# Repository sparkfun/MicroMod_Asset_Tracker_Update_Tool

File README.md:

# MicroMod Asset Tracker Firmware Update Tool

[*SparkFun MicroMod Update Tool (DEV-17725)*](https://www.sparkfun.com/products/17725)

A dummy Processor Board which will simplify firmware updates for the SARA-R5 on the [MicroMod Asset Tracker Carrier Board](https://www.sparkfun.com/products/17272).

The board carries a CH340C USB-Serial converter to act as the bridge between the USB-C interface on the carrier board and the 8-wire UART interface on the SARA-R5.

Power for the SARA can be enabled via a push-button on the carrier board.

The firmware can be updated with [EasyFlash](https://www.u-blox.com/sites/default/files/SARA-R5-FW-Update_AppNote_%28UBX-20033314%29.pdf).

The tool will also make it easy for anyone wanting to use [m-center](https://www.u-blox.com/en/product/m-center) to communicate with the SARA.

## Repository Contents

* **/Hardware** - Eagle PCB, SCH and LBR design files
* **LICENSE.md** contains the licence information

## Documentation

* **[Hookup Guide](https://learn.sparkfun.com/tutorials/micromod-update-tool-hookup-guide)** - A basic Hookup Guide for the MicroMod Update Tool.
* **[Getting Started with MicroMod](https://learn.sparkfun.com/tutorials/getting-started-with-micromod)** - A tutorial to help you get started with the MicroMod Ecosystem.
* **[Designing with MicroMod](https://learn.sparkfun.com/tutorials/designing-with-micromod)** - A tutorial to walk you through the specs of the MicroMod processor and carrier board as well as the basics of incorporating the MicroMod form factor into your own PCB designs.

## Product Versions

* **[DEV-17725](https://www.sparkfun.com/products/17725)** - Initial release of the MicroMod Update Tool

## License Information

This product is _**open source**_!

Please review the LICENSE.md file for license information.

If you have any questions or concerns on licensing, please contact technical support on our [SparkFun forums](https://forum.sparkfun.com/viewforum.php?f=152).

Distributed as-is; no warranty is given.

- Your friends at SparkFun.

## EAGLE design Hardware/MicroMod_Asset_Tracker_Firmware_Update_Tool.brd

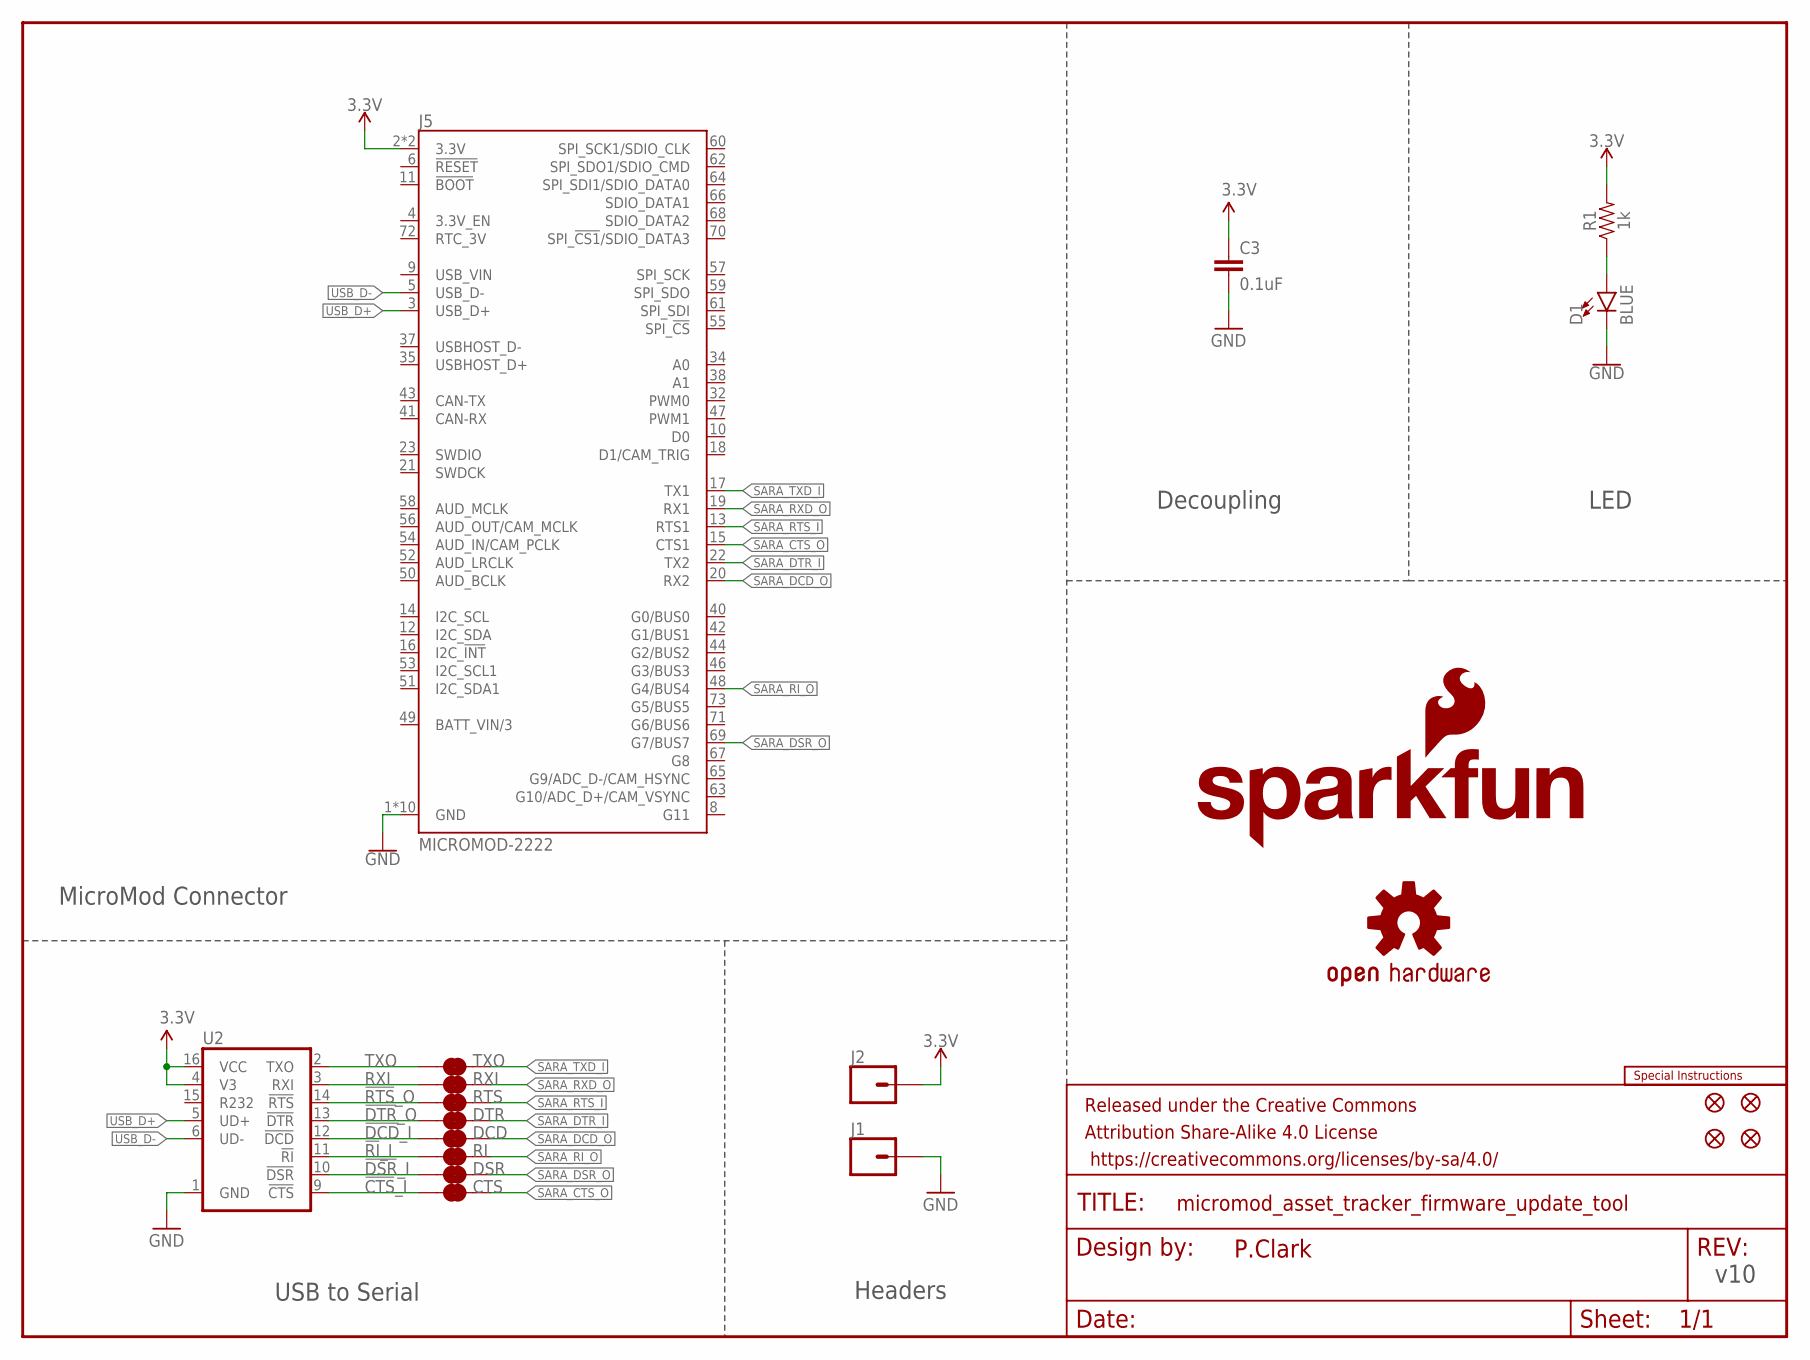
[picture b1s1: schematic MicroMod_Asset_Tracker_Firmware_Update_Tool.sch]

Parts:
C3: 0.1uF; 0603
CTS: JUMPER-COMBO_2_NC_TRACE; COMBO-JUMPER_2_NC_TRACE
D1: BLUE; LED-0603
DCD: JUMPER-COMBO_2_NC_TRACE; COMBO-JUMPER_2_NC_TRACE
DSR: JUMPER-COMBO_2_NC_TRACE; COMBO-JUMPER_2_NC_TRACE
DTR: JUMPER-COMBO_2_NC_TRACE; COMBO-JUMPER_2_NC_TRACE
FRAME1: FRAME-LETTER; CREATIVE_COMMONS
J1, J2: CONN_01PTH_NO_SILK_YES_STOP; 1X01_NO_SILK
J5: MICROMOD-2222; M.2-CARD-E-22
JP3, JP4, JP5, JP6: FIDUCIAL1X2; FIDUCIAL-1X2
LOGO1: OSHW-LOGOMINI; OSHW-LOGO-MINI
LOGO2: SPECIAL_INSTRUCTIONS-ORDERING; ORDERING_INSTRUCTIONS
LOGO3: SFE_LOGO_NAME_FLAME.1_INCH; SFE_LOGO_NAME_FLAME_.1
R1: 1k; 0603
RI: JUMPER-COMBO_2_NC_TRACE; COMBO-JUMPER_2_NC_TRACE
RTS: JUMPER-COMBO_2_NC_TRACE; COMBO-JUMPER_2_NC_TRACE
RXI: JUMPER-COMBO_2_NC_TRACE; COMBO-JUMPER_2_NC_TRACE
TXO: JUMPER-COMBO_2_NC_TRACE; COMBO-JUMPER_2_NC_TRACE
U2: CH340C; SO016

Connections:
3.3V: C3.1, J2.1, J5.2 (3.3V), J5.74 (3.3V), R1.2, U2.4 (V3), U2.16 (VCC)
!CTS!_I: CTS.1, CTS.3 (1), U2.9 (!CTS)
!DCD!_I: DCD.1, DCD.3 (1), U2.12 (!DCD)
!DSR!_I: DSR.1, DSR.3 (1), U2.10 (!DSR)
!DTR!_O: DTR.1, DTR.3 (1), U2.13 (!DTR)
!RI!_I: RI.1, RI.3 (1), U2.11 (!RI)
!RTS!_O: RTS.1, RTS.3 (1), U2.14 (!RTS)
GND: C3.2, D1.C, J1.1, J5.1 (GND), J5.7 (GND), J5.33 (GND), J5.36 (GND), J5.39 (GND), J5.45 (GND), J5.75 (GND), J5.GND1 (GND), J5.GND2 (GND), J5.GND3 (GND), U2.1 (GND)
unnamed: D1.A, R1.1
RXI: RXI.1, RXI.3 (1), U2.3 (RXI)
SARA_CTS_O: CTS.2, CTS.4 (2), J5.15 (CTS1)
SARA_DCD_O: DCD.2, DCD.4 (2), J5.20 (RX2)
SARA_DSR_O: DSR.2, DSR.4 (2), J5.69 (G7/BUS7)
SARA_DTR_I: DTR.2, DTR.4 (2), J5.22 (TX2)
SARA_RI_O: J5.48 (G4/BUS4), RI.2, RI.4 (2)
SARA_RTS_I: J5.13 (RTS1), RTS.2, RTS.4 (2)
SARA_RXD_O: J5.19 (RX1), RXI.2, RXI.4 (2)
SARA_TXD_I: J5.17 (TX1), TXO.2, TXO.4 (2)
TXO: TXO.1, TXO.3 (1), U2.2 (TXO)
USB_D+: J5.3 (USB_D+), U2.5 (UD+)
USB_D-: J5.5 (USB_D-), U2.6 (UD-)

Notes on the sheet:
v10
USB to Serial
P.Clark
Headers
LED
Decoupling
MicroMod Connector

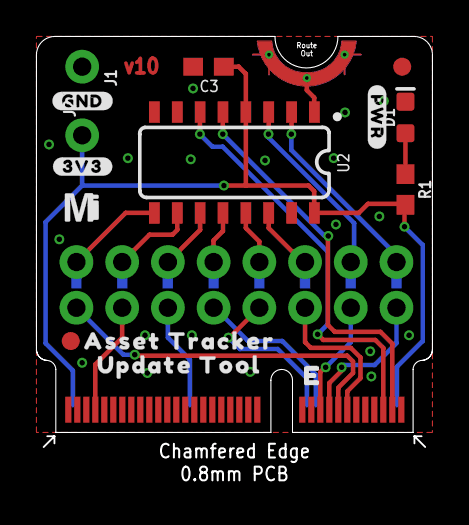
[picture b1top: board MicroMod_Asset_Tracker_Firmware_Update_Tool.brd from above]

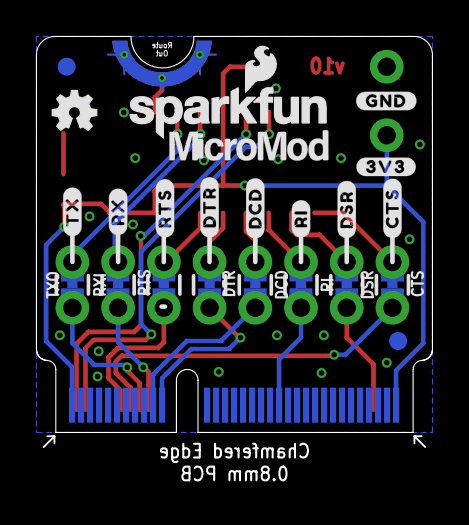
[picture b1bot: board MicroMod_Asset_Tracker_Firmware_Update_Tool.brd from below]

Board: 4 copper layers, 22.0 x 22.8 mm, 40 parts (23 on the bottom side), 21 nets.

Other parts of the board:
U$1: #TX#0
U$2: #RX#0
U$3, U$7: #GND#2
U$4: #DTR#0
U$5: #RI#0
U$6, U$17: #3V3#3
U$8: #PWR#0
U$9: MICROMOD_MI_LOGO_.35
U$10: ASSET_TRACKER0
U$11: UPDATE_TOOL0
U$12: MICROMOD_LOGO_.35
U$14: #CTS#0
U$18: #DSR#0
U$20: #RTS#0
U$23: #DCD#0

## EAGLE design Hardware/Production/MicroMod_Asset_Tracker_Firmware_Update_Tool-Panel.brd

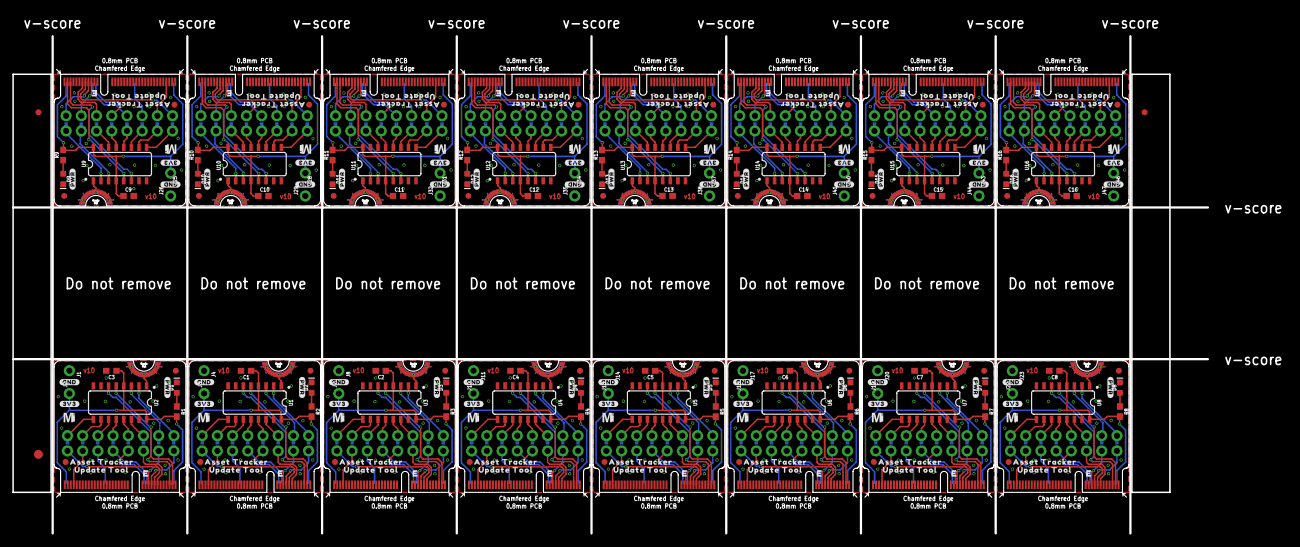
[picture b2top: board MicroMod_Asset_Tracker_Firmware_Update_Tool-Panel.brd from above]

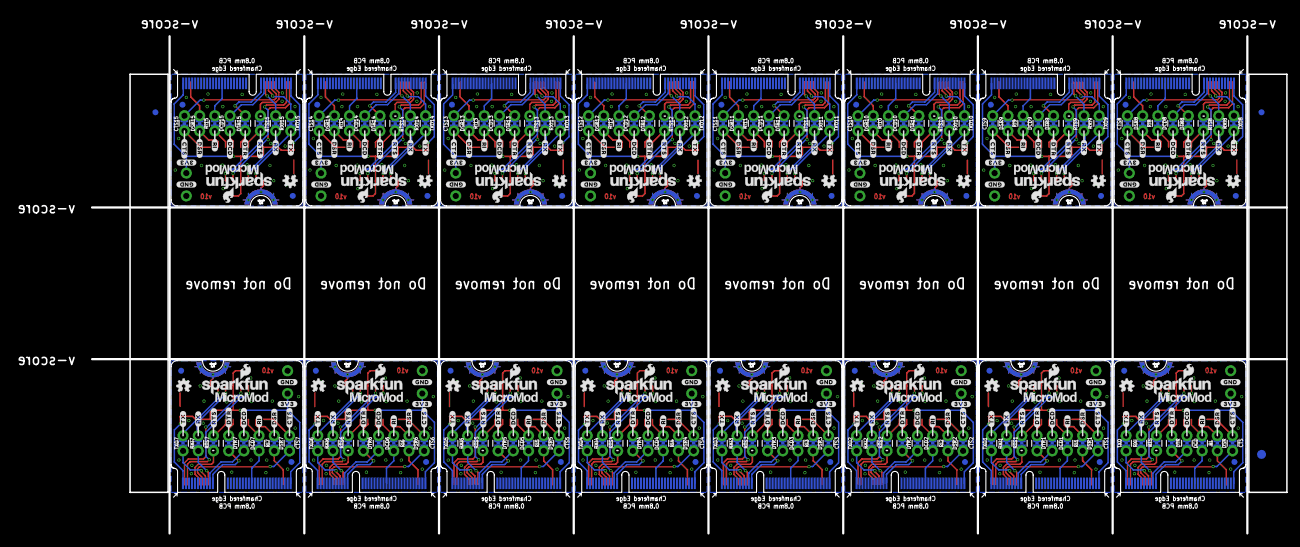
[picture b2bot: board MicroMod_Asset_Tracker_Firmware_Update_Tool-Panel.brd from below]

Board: 4 copper layers, 199.6 x 83.1 mm, 614 parts (371 on the bottom side), 336 nets.

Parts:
C1, C2, C3, C4, C5, C6, C7, C8, C9, C10, C11, C12, C13, C14, C15, C16: 0.1uF; 0603
CTS, CTS1, CTS2, CTS3, CTS4, CTS5, CTS6, CTS7, CTS8, CTS9, CTS10, CTS11, CTS12, CTS13, CTS14, CTS15: JUMPER-COMBO_2_NC_TRACE; COMBO-JUMPER_2_NC_TRACE
D1, D2, D3, D4, D5, D6, D7, D8, D9, D10, D11, D12, D13, D14, D15, D16: BLUE; LED-0603
DCD, DCD1, DCD2, DCD3, DCD4, DCD5, DCD6, DCD7, DCD8, DCD9, DCD10, DCD11, DCD12, DCD13, DCD14, DCD15: JUMPER-COMBO_2_NC_TRACE; COMBO-JUMPER_2_NC_TRACE
DSR, DSR1, DSR2, DSR3, DSR4, DSR5, DSR6, DSR7, DSR8, DSR9, DSR10, DSR11, DSR12, DSR13, DSR14, DSR15: JUMPER-COMBO_2_NC_TRACE; COMBO-JUMPER_2_NC_TRACE
DTR, DTR1, DTR2, DTR3, DTR4, DTR5, DTR6, DTR7, DTR8, DTR9, DTR10, DTR11, DTR12, DTR13, DTR14, DTR15: JUMPER-COMBO_2_NC_TRACE; COMBO-JUMPER_2_NC_TRACE
E$1, E$2, E$3, E$4: FIDUCIAL-1X2
E$5, E$6: FIDUCIAL-1.5X3
J1, J2, J3, J4, J7, J8, J10, J11, J13, J14, J16, J17, J19, J20, J22, J23, J25, J26, J28, J29, J31, J32, J34, J35, J37, J38, J40, J41, J43, J44, J46, J47: 1X01_NO_SILK
J5, J6, J9, J12, J15, J18, J21, J24, J27, J30, J33, J36, J39, J42, J45, J48: MICROMOD-2222; M.2-CARD-E-22
JP1, JP2, JP3, JP4, JP5, JP6, JP7, JP8, JP9, JP10, JP11, JP12, JP13, JP14, JP15, JP16, JP17, JP18, JP19, JP20, JP21, JP22, JP23, JP24, JP25, JP26, JP27, JP28, JP29, JP30, JP31, JP32, JP33, JP34, JP35, JP36, JP37, JP38, JP39, JP40, JP41, JP42, JP43, JP44, JP45, JP46, JP47, JP48, JP49, JP50, JP51, JP52, JP53, JP54, JP55, JP56, JP57, JP58, JP59, JP60, JP61, JP62, JP63, JP64: FIDUCIAL1X2; FIDUCIAL-1X2
LOGO1, LOGO2, LOGO5, LOGO7, LOGO9, LOGO11, LOGO13, LOGO15, LOGO17, LOGO19, LOGO21, LOGO23, LOGO25, LOGO27, LOGO29, LOGO31: OSHW-LOGOMINI; OSHW-LOGO-MINI
LOGO3, LOGO4, LOGO6, LOGO8, LOGO10, LOGO12, LOGO14, LOGO16, LOGO18, LOGO20, LOGO22, LOGO24, LOGO26, LOGO28, LOGO30, LOGO32: SFE_LOGO_NAME_FLAME.1_INCH; SFE_LOGO_NAME_FLAME_.1
R1, R2, R3, R4, R5, R6, R7, R8, R9, R10, R11, R12, R13, R14, R15, R16: 1k; 0603
RI, RI1, RI2, RI3, RI4, RI5, RI6, RI7, RI8, RI9, RI10, RI11, RI12, RI13, RI14, RI15: JUMPER-COMBO_2_NC_TRACE; COMBO-JUMPER_2_NC_TRACE
RTS, RTS1, RTS2, RTS3, RTS4, RTS5, RTS6, RTS7, RTS8, RTS9, RTS10, RTS11, RTS12, RTS13, RTS14, RTS15: JUMPER-COMBO_2_NC_TRACE; COMBO-JUMPER_2_NC_TRACE
RXI, RXI1, RXI2, RXI3, RXI4, RXI5, RXI6, RXI7, RXI8, RXI9, RXI10, RXI11, RXI12, RXI13, RXI14, RXI15: JUMPER-COMBO_2_NC_TRACE; COMBO-JUMPER_2_NC_TRACE
TXO, TXO1, TXO2, TXO3, TXO4, TXO5, TXO6, TXO7, TXO8, TXO9, TXO10, TXO11, TXO12, TXO13, TXO14, TXO15: JUMPER-COMBO_2_NC_TRACE; COMBO-JUMPER_2_NC_TRACE
U1, U2, U3, U4, U5, U6, U7, U8, U9, U10, U11, U12, U13, U14, U15, U16: CH340C; SO016
U$1, U$24, U$41, U$58, U$75, U$92, U$109, U$126, U$143, U$160, U$177, U$194, U$211, U$228, U$245, U$262: #TX#0
U$2, U$25, U$42, U$59, U$76, U$93, U$110, U$127, U$144, U$161, U$178, U$195, U$212, U$229, U$246, U$263: #RX#0
U$3, U$7, U$13, U$29, U$35, U$46, U$52, U$63, U$69, U$80, U$86, U$97, U$103, U$114, U$120, U$131, U$137, U$148, U$154, U$165, U$171, U$182, U$188, U$199, U$205, U$216, U$222, U$233, U$239, U$250, U$256, U$267: #GND#2
U$4, U$26, U$43, U$60, U$77, U$94, U$111, U$128, U$145, U$162, U$179, U$196, U$213, U$230, U$247, U$264: #DTR#0
U$5, U$27, U$44, U$61, U$78, U$95, U$112, U$129, U$146, U$163, U$180, U$197, U$214, U$231, U$248, U$265: #RI#0
U$6, U$15, U$17, U$28, U$36, U$45, U$53, U$62, U$70, U$79, U$87, U$96, U$104, U$113, U$121, U$130, U$138, U$147, U$155, U$164, U$172, U$181, U$189, U$198, U$206, U$215, U$223, U$232, U$240, U$249, U$257, U$266: #3V3#3
U$8, U$30, U$47, U$64, U$81, U$98, U$115, U$132, U$149, U$166, U$183, U$200, U$217, U$234, U$251, U$268: #PWR#0
U$9, U$31, U$48, U$65, U$82, U$99, U$116, U$133, U$150, U$167, U$184, U$201, U$218, U$235, U$252, U$269: MICROMOD_MI_LOGO_.35
U$10, U$32, U$49, U$66, U$83, U$100, U$117, U$134, U$151, U$168, U$185, U$202, U$219, U$236, U$253, U$270: ASSET_TRACKER0
U$11, U$33, U$50, U$67, U$84, U$101, U$118, U$135, U$152, U$169, U$186, U$203, U$220, U$237, U$254, U$271: UPDATE_TOOL0
U$12, U$34, U$51, U$68, U$85, U$102, U$119, U$136, U$153, U$170, U$187, U$204, U$221, U$238, U$255, U$272: MICROMOD_LOGO_.35
U$14, U$16, U$37, U$54, U$71, U$88, U$105, U$122, U$139, U$156, U$173, U$190, U$207, U$224, U$241, U$258: #CTS#0
U$18, U$19, U$38, U$55, U$72, U$89, U$106, U$123, U$140, U$157, U$174, U$191, U$208, U$225, U$242, U$259: #DSR#0
U$20, U$21, U$39, U$56, U$73, U$90, U$107, U$124, U$141, U$158, U$175, U$192, U$209, U$226, U$243, U$260: #RTS#0
U$22, U$23, U$40, U$57, U$74, U$91, U$108, U$125, U$142, U$159, U$176, U$193, U$210, U$227, U$244, U$261: #DCD#0

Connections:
3.3V: C3.1, J2.1, J5.2, J5.74, R1.2, U2.4, U2.16
3.3V1: C1.1, J3.1, J6.2, J6.74, R2.2, U1.4, U1.16
3.3V2: C2.1, J7.1, J9.2, J9.74, R3.2, U3.4, U3.16
3.3V3: C4.1, J10.1, J12.2, J12.74, R4.2, U4.4, U4.16
3.3V4: C5.1, J13.1, J15.2, J15.74, R5.2, U5.4, U5.16
3.3V5: C6.1, J16.1, J18.2, J18.74, R6.2, U6.4, U6.16
3.3V6: C7.1, J19.1, J21.2, J21.74, R7.2, U7.4, U7.16
3.3V7: C8.1, J22.1, J24.2, J24.74, R8.2, U8.4, U8.16
3.3V8: C9.1, J25.1, J27.2, J27.74, R9.2, U9.4, U9.16
3.3V9: C10.1, J28.1, J30.2, J30.74, R10.2, U10.4, U10.16
3.3V10: C11.1, J31.1, J33.2, J33.74, R11.2, U11.4, U11.16
3.3V11: C12.1, J34.1, J36.2, J36.74, R12.2, U12.4, U12.16
3.3V12: C13.1, J37.1, J39.2, J39.74, R13.2, U13.4, U13.16
3.3V13: C14.1, J40.1, J42.2, J42.74, R14.2, U14.4, U14.16
3.3V14: C15.1, J43.1, J45.2, J45.74, R15.2, U15.4, U15.16
3.3V15: C16.1, J46.1, J48.2, J48.74, R16.2, U16.4, U16.16
!CTS!_I: CTS.1, CTS.3, U2.9
!CTS!_I1: CTS1.1, CTS1.3, U1.9
!CTS!_I2: CTS2.1, CTS2.3, U3.9
!CTS!_I3: CTS3.1, CTS3.3, U4.9
!CTS!_I4: CTS4.1, CTS4.3, U5.9
!CTS!_I5: CTS5.1, CTS5.3, U6.9
!CTS!_I6: CTS6.1, CTS6.3, U7.9
!CTS!_I7: CTS7.1, CTS7.3, U8.9
!CTS!_I8: CTS8.1, CTS8.3, U9.9
!CTS!_I9: CTS9.1, CTS9.3, U10.9
!CTS!_I10: CTS10.1, CTS10.3, U11.9
!CTS!_I11: CTS11.1, CTS11.3, U12.9
!CTS!_I12: CTS12.1, CTS12.3, U13.9
!CTS!_I13: CTS13.1, CTS13.3, U14.9
!CTS!_I14: CTS14.1, CTS14.3, U15.9
!CTS!_I15: CTS15.1, CTS15.3, U16.9
!DCD!_I: DCD.1, DCD.3, U2.12
!DCD!_I1: DCD1.1, DCD1.3, U1.12
!DCD!_I2: DCD2.1, DCD2.3, U3.12
!DCD!_I3: DCD3.1, DCD3.3, U4.12
!DCD!_I4: DCD4.1, DCD4.3, U5.12
!DCD!_I5: DCD5.1, DCD5.3, U6.12
!DCD!_I6: DCD6.1, DCD6.3, U7.12
!DCD!_I7: DCD7.1, DCD7.3, U8.12
!DCD!_I8: DCD8.1, DCD8.3, U9.12
!DCD!_I9: DCD9.1, DCD9.3, U10.12
!DCD!_I10: DCD10.1, DCD10.3, U11.12
!DCD!_I11: DCD11.1, DCD11.3, U12.12
!DCD!_I12: DCD12.1, DCD12.3, U13.12
!DCD!_I13: DCD13.1, DCD13.3, U14.12
!DCD!_I14: DCD14.1, DCD14.3, U15.12
!DCD!_I15: DCD15.1, DCD15.3, U16.12
!DSR!_I: DSR.1, DSR.3, U2.10
!DSR!_I1: DSR1.1, DSR1.3, U1.10
!DSR!_I2: DSR2.1, DSR2.3, U3.10
!DSR!_I3: DSR3.1, DSR3.3, U4.10
!DSR!_I4: DSR4.1, DSR4.3, U5.10
!DSR!_I5: DSR5.1, DSR5.3, U6.10
!DSR!_I6: DSR6.1, DSR6.3, U7.10
!DSR!_I7: DSR7.1, DSR7.3, U8.10
!DSR!_I8: DSR8.1, DSR8.3, U9.10
!DSR!_I9: DSR9.1, DSR9.3, U10.10
!DSR!_I10: DSR10.1, DSR10.3, U11.10
!DSR!_I11: DSR11.1, DSR11.3, U12.10
!DSR!_I12: DSR12.1, DSR12.3, U13.10
!DSR!_I13: DSR13.1, DSR13.3, U14.10
!DSR!_I14: DSR14.1, DSR14.3, U15.10
!DSR!_I15: DSR15.1, DSR15.3, U16.10
!DTR!_O: DTR.1, DTR.3, U2.13
!DTR!_O1: DTR1.1, DTR1.3, U1.13
!DTR!_O2: DTR2.1, DTR2.3, U3.13
!DTR!_O3: DTR3.1, DTR3.3, U4.13
!DTR!_O4: DTR4.1, DTR4.3, U5.13
!DTR!_O5: DTR5.1, DTR5.3, U6.13
!DTR!_O6: DTR6.1, DTR6.3, U7.13
!DTR!_O7: DTR7.1, DTR7.3, U8.13
!DTR!_O8: DTR8.1, DTR8.3, U9.13
!DTR!_O9: DTR9.1, DTR9.3, U10.13
!DTR!_O10: DTR10.1, DTR10.3, U11.13
!DTR!_O11: DTR11.1, DTR11.3, U12.13
!DTR!_O12: DTR12.1, DTR12.3, U13.13
!DTR!_O13: DTR13.1, DTR13.3, U14.13
!DTR!_O14: DTR14.1, DTR14.3, U15.13
!DTR!_O15: DTR15.1, DTR15.3, U16.13
!RI!_I: RI.1, RI.3, U2.11
!RI!_I1: RI1.1, RI1.3, U1.11
!RI!_I2: RI2.1, RI2.3, U3.11
!RI!_I3: RI3.1, RI3.3, U4.11
!RI!_I4: RI4.1, RI4.3, U5.11
!RI!_I5: RI5.1, RI5.3, U6.11
!RI!_I6: RI6.1, RI6.3, U7.11
!RI!_I7: RI7.1, RI7.3, U8.11
!RI!_I8: RI8.1, RI8.3, U9.11
!RI!_I9: RI9.1, RI9.3, U10.11
!RI!_I10: RI10.1, RI10.3, U11.11
!RI!_I11: RI11.1, RI11.3, U12.11
!RI!_I12: RI12.1, RI12.3, U13.11
!RI!_I13: RI13.1, RI13.3, U14.11
!RI!_I14: RI14.1, RI14.3, U15.11
!RI!_I15: RI15.1, RI15.3, U16.11
!RTS!_O: RTS.1, RTS.3, U2.14
!RTS!_O1: RTS1.1, RTS1.3, U1.14
!RTS!_O2: RTS2.1, RTS2.3, U3.14
!RTS!_O3: RTS3.1, RTS3.3, U4.14
!RTS!_O4: RTS4.1, RTS4.3, U5.14
!RTS!_O5: RTS5.1, RTS5.3, U6.14
!RTS!_O6: RTS6.1, RTS6.3, U7.14
!RTS!_O7: RTS7.1, RTS7.3, U8.14
!RTS!_O8: RTS8.1, RTS8.3, U9.14
!RTS!_O9: RTS9.1, RTS9.3, U10.14
!RTS!_O10: RTS10.1, RTS10.3, U11.14
!RTS!_O11: RTS11.1, RTS11.3, U12.14
!RTS!_O12: RTS12.1, RTS12.3, U13.14
!RTS!_O13: RTS13.1, RTS13.3, U14.14
!RTS!_O14: RTS14.1, RTS14.3, U15.14
!RTS!_O15: RTS15.1, RTS15.3, U16.14
GND: C3.2, D1.C, J1.1, J5.1, J5.7, J5.33, J5.36, J5.39, J5.45, J5.75, J5.GND1, J5.GND2, J5.GND3, U2.1
GND1: C1.2, D2.C, J4.1, J6.1, J6.7, J6.33, J6.36, J6.39, J6.45, J6.75, J6.GND1, J6.GND2, J6.GND3, U1.1
GND2: C2.2, D3.C, J8.1, J9.1, J9.7, J9.33, J9.36, J9.39, J9.45, J9.75, J9.GND1, J9.GND2, J9.GND3, U3.1
GND3: C4.2, D4.C, J11.1, J12.1, J12.7, J12.33, J12.36, J12.39, J12.45, J12.75, J12.GND1, J12.GND2, J12.GND3, U4.1
GND4: C5.2, D5.C, J14.1, J15.1, J15.7, J15.33, J15.36, J15.39, J15.45, J15.75, J15.GND1, J15.GND2, J15.GND3, U5.1
GND5: C6.2, D6.C, J17.1, J18.1, J18.7, J18.33, J18.36, J18.39, J18.45, J18.75, J18.GND1, J18.GND2, J18.GND3, U6.1
GND6: C7.2, D7.C, J20.1, J21.1, J21.7, J21.33, J21.36, J21.39, J21.45, J21.75, J21.GND1, J21.GND2, J21.GND3, U7.1
GND7: C8.2, D8.C, J23.1, J24.1, J24.7, J24.33, J24.36, J24.39, J24.45, J24.75, J24.GND1, J24.GND2, J24.GND3, U8.1
GND8: C9.2, D9.C, J26.1, J27.1, J27.7, J27.33, J27.36, J27.39, J27.45, J27.75, J27.GND1, J27.GND2, J27.GND3, U9.1
GND9: C10.2, D10.C, J29.1, J30.1, J30.7, J30.33, J30.36, J30.39, J30.45, J30.75, J30.GND1, J30.GND2, J30.GND3, U10.1
GND10: C11.2, D11.C, J32.1, J33.1, J33.7, J33.33, J33.36, J33.39, J33.45, J33.75, J33.GND1, J33.GND2, J33.GND3, U11.1
GND11: C12.2, D12.C, J35.1, J36.1, J36.7, J36.33, J36.36, J36.39, J36.45, J36.75, J36.GND1, J36.GND2, J36.GND3, U12.1
GND12: C13.2, D13.C, J38.1, J39.1, J39.7, J39.33, J39.36, J39.39, J39.45, J39.75, J39.GND1, J39.GND2, J39.GND3, U13.1
GND13: C14.2, D14.C, J41.1, J42.1, J42.7, J42.33, J42.36, J42.39, J42.45, J42.75, J42.GND1, J42.GND2, J42.GND3, U14.1
GND14: C15.2, D15.C, J44.1, J45.1, J45.7, J45.33, J45.36, J45.39, J45.45, J45.75, J45.GND1, J45.GND2, J45.GND3, U15.1
GND15: C16.2, D16.C, J47.1, J48.1, J48.7, J48.33, J48.36, J48.39, J48.45, J48.75, J48.GND1, J48.GND2, J48.GND3, U16.1
unnamed: D2.A, R2.1
unnamed: D3.A, R3.1
unnamed: D1.A, R1.1
unnamed: D4.A, R4.1
unnamed: D5.A, R5.1
unnamed: D6.A, R6.1
unnamed: D7.A, R7.1
unnamed: D8.A, R8.1
unnamed: D9.A, R9.1
unnamed: D10.A, R10.1
unnamed: D11.A, R11.1
unnamed: D12.A, R12.1
unnamed: D13.A, R13.1
unnamed: D14.A, R14.1
unnamed: D15.A, R15.1
unnamed: D16.A, R16.1
RXI: RXI.1, RXI.3, U2.3
RXI1: RXI1.1, RXI1.3, U1.3
RXI2: RXI2.1, RXI2.3, U3.3
RXI3: RXI3.1, RXI3.3, U4.3
RXI4: RXI4.1, RXI4.3, U5.3
RXI5: RXI5.1, RXI5.3, U6.3
RXI6: RXI6.1, RXI6.3, U7.3
RXI7: RXI7.1, RXI7.3, U8.3
RXI8: RXI8.1, RXI8.3, U9.3
RXI9: RXI9.1, RXI9.3, U10.3
RXI10: RXI10.1, RXI10.3, U11.3
RXI11: RXI11.1, RXI11.3, U12.3
RXI12: RXI12.1, RXI12.3, U13.3
RXI13: RXI13.1, RXI13.3, U14.3
RXI14: RXI14.1, RXI14.3, U15.3
RXI15: RXI15.1, RXI15.3, U16.3
SARA_CTS_O: CTS.2, CTS.4, J5.15
SARA_CTS_O1: CTS1.2, CTS1.4, J6.15
SARA_CTS_O2: CTS2.2, CTS2.4, J9.15
SARA_CTS_O3: CTS3.2, CTS3.4, J12.15
SARA_CTS_O4: CTS4.2, CTS4.4, J15.15
SARA_CTS_O5: CTS5.2, CTS5.4, J18.15
SARA_CTS_O6: CTS6.2, CTS6.4, J21.15
SARA_CTS_O7: CTS7.2, CTS7.4, J24.15
SARA_CTS_O8: CTS8.2, CTS8.4, J27.15
SARA_CTS_O9: CTS9.2, CTS9.4, J30.15
SARA_CTS_O10: CTS10.2, CTS10.4, J33.15
SARA_CTS_O11: CTS11.2, CTS11.4, J36.15
SARA_CTS_O12: CTS12.2, CTS12.4, J39.15
SARA_CTS_O13: CTS13.2, CTS13.4, J42.15
SARA_CTS_O14: CTS14.2, CTS14.4, J45.15
SARA_CTS_O15: CTS15.2, CTS15.4, J48.15
SARA_DCD_O: DCD.2, DCD.4, J5.20
SARA_DCD_O1: DCD1.2, DCD1.4, J6.20
SARA_DCD_O2: DCD2.2, DCD2.4, J9.20
SARA_DCD_O3: DCD3.2, DCD3.4, J12.20
SARA_DCD_O4: DCD4.2, DCD4.4, J15.20
SARA_DCD_O5: DCD5.2, DCD5.4, J18.20
SARA_DCD_O6: DCD6.2, DCD6.4, J21.20
SARA_DCD_O7: DCD7.2, DCD7.4, J24.20
SARA_DCD_O8: DCD8.2, DCD8.4, J27.20
SARA_DCD_O9: DCD9.2, DCD9.4, J30.20
SARA_DCD_O10: DCD10.2, DCD10.4, J33.20
SARA_DCD_O11: DCD11.2, DCD11.4, J36.20
SARA_DCD_O12: DCD12.2, DCD12.4, J39.20
SARA_DCD_O13: DCD13.2, DCD13.4, J42.20
SARA_DCD_O14: DCD14.2, DCD14.4, J45.20
SARA_DCD_O15: DCD15.2, DCD15.4, J48.20
SARA_DSR_O: DSR.2, DSR.4, J5.69
SARA_DSR_O1: DSR1.2, DSR1.4, J6.69
SARA_DSR_O2: DSR2.2, DSR2.4, J9.69
SARA_DSR_O3: DSR3.2, DSR3.4, J12.69
SARA_DSR_O4: DSR4.2, DSR4.4, J15.69
SARA_DSR_O5: DSR5.2, DSR5.4, J18.69
SARA_DSR_O6: DSR6.2, DSR6.4, J21.69
SARA_DSR_O7: DSR7.2, DSR7.4, J24.69
SARA_DSR_O8: DSR8.2, DSR8.4, J27.69
SARA_DSR_O9: DSR9.2, DSR9.4, J30.69
SARA_DSR_O10: DSR10.2, DSR10.4, J33.69
SARA_DSR_O11: DSR11.2, DSR11.4, J36.69
SARA_DSR_O12: DSR12.2, DSR12.4, J39.69
SARA_DSR_O13: DSR13.2, DSR13.4, J42.69
SARA_DSR_O14: DSR14.2, DSR14.4, J45.69
SARA_DSR_O15: DSR15.2, DSR15.4, J48.69
SARA_DTR_I: DTR.2, DTR.4, J5.22
SARA_DTR_I1: DTR1.2, DTR1.4, J6.22
SARA_DTR_I2: DTR2.2, DTR2.4, J9.22
SARA_DTR_I3: DTR3.2, DTR3.4, J12.22
SARA_DTR_I4: DTR4.2, DTR4.4, J15.22
SARA_DTR_I5: DTR5.2, DTR5.4, J18.22
SARA_DTR_I6: DTR6.2, DTR6.4, J21.22
SARA_DTR_I7: DTR7.2, DTR7.4, J24.22
SARA_DTR_I8: DTR8.2, DTR8.4, J27.22
SARA_DTR_I9: DTR9.2, DTR9.4, J30.22
SARA_DTR_I10: DTR10.2, DTR10.4, J33.22
SARA_DTR_I11: DTR11.2, DTR11.4, J36.22
SARA_DTR_I12: DTR12.2, DTR12.4, J39.22
SARA_DTR_I13: DTR13.2, DTR13.4, J42.22
SARA_DTR_I14: DTR14.2, DTR14.4, J45.22
SARA_DTR_I15: DTR15.2, DTR15.4, J48.22
SARA_RI_O: J5.48, RI.2, RI.4
SARA_RI_O1: J6.48, RI1.2, RI1.4
SARA_RI_O2: J9.48, RI2.2, RI2.4
SARA_RI_O3: J12.48, RI3.2, RI3.4
SARA_RI_O4: J15.48, RI4.2, RI4.4
SARA_RI_O5: J18.48, RI5.2, RI5.4
SARA_RI_O6: J21.48, RI6.2, RI6.4
SARA_RI_O7: J24.48, RI7.2, RI7.4
SARA_RI_O8: J27.48, RI8.2, RI8.4
SARA_RI_O9: J30.48, RI9.2, RI9.4
SARA_RI_O10: J33.48, RI10.2, RI10.4
SARA_RI_O11: J36.48, RI11.2, RI11.4
SARA_RI_O12: J39.48, RI12.2, RI12.4
SARA_RI_O13: J42.48, RI13.2, RI13.4
SARA_RI_O14: J45.48, RI14.2, RI14.4
SARA_RI_O15: J48.48, RI15.2, RI15.4
SARA_RTS_I: J5.13, RTS.2, RTS.4
SARA_RTS_I1: J6.13, RTS1.2, RTS1.4
SARA_RTS_I2: J9.13, RTS2.2, RTS2.4
SARA_RTS_I3: J12.13, RTS3.2, RTS3.4
SARA_RTS_I4: J15.13, RTS4.2, RTS4.4
SARA_RTS_I5: J18.13, RTS5.2, RTS5.4
SARA_RTS_I6: J21.13, RTS6.2, RTS6.4
SARA_RTS_I7: J24.13, RTS7.2, RTS7.4
SARA_RTS_I8: J27.13, RTS8.2, RTS8.4
SARA_RTS_I9: J30.13, RTS9.2, RTS9.4
SARA_RTS_I10: J33.13, RTS10.2, RTS10.4
SARA_RTS_I11: J36.13, RTS11.2, RTS11.4
SARA_RTS_I12: J39.13, RTS12.2, RTS12.4
SARA_RTS_I13: J42.13, RTS13.2, RTS13.4
SARA_RTS_I14: J45.13, RTS14.2, RTS14.4
SARA_RTS_I15: J48.13, RTS15.2, RTS15.4
SARA_RXD_O: J5.19, RXI.2, RXI.4
SARA_RXD_O1: J6.19, RXI1.2, RXI1.4
SARA_RXD_O2: J9.19, RXI2.2, RXI2.4
SARA_RXD_O3: J12.19, RXI3.2, RXI3.4
SARA_RXD_O4: J15.19, RXI4.2, RXI4.4
SARA_RXD_O5: J18.19, RXI5.2, RXI5.4
SARA_RXD_O6: J21.19, RXI6.2, RXI6.4
SARA_RXD_O7: J24.19, RXI7.2, RXI7.4
SARA_RXD_O8: J27.19, RXI8.2, RXI8.4
SARA_RXD_O9: J30.19, RXI9.2, RXI9.4
SARA_RXD_O10: J33.19, RXI10.2, RXI10.4
SARA_RXD_O11: J36.19, RXI11.2, RXI11.4
SARA_RXD_O12: J39.19, RXI12.2, RXI12.4
SARA_RXD_O13: J42.19, RXI13.2, RXI13.4
SARA_RXD_O14: J45.19, RXI14.2, RXI14.4
SARA_RXD_O15: J48.19, RXI15.2, RXI15.4
SARA_TXD_I: J5.17, TXO.2, TXO.4
SARA_TXD_I1: J6.17, TXO1.2, TXO1.4
SARA_TXD_I2: J9.17, TXO2.2, TXO2.4
SARA_TXD_I3: J12.17, TXO3.2, TXO3.4
SARA_TXD_I4: J15.17, TXO4.2, TXO4.4
SARA_TXD_I5: J18.17, TXO5.2, TXO5.4
SARA_TXD_I6: J21.17, TXO6.2, TXO6.4
SARA_TXD_I7: J24.17, TXO7.2, TXO7.4
SARA_TXD_I8: J27.17, TXO8.2, TXO8.4
SARA_TXD_I9: J30.17, TXO9.2, TXO9.4
SARA_TXD_I10: J33.17, TXO10.2, TXO10.4
SARA_TXD_I11: J36.17, TXO11.2, TXO11.4
SARA_TXD_I12: J39.17, TXO12.2, TXO12.4
SARA_TXD_I13: J42.17, TXO13.2, TXO13.4
SARA_TXD_I14: J45.17, TXO14.2, TXO14.4
SARA_TXD_I15: J48.17, TXO15.2, TXO15.4
TXO: TXO.1, TXO.3, U2.2
TXO1: TXO1.1, TXO1.3, U1.2
TXO2: TXO2.1, TXO2.3, U3.2
TXO3: TXO3.1, TXO3.3, U4.2
TXO4: TXO4.1, TXO4.3, U5.2
TXO5: TXO5.1, TXO5.3, U6.2
TXO6: TXO6.1, TXO6.3, U7.2
TXO7: TXO7.1, TXO7.3, U8.2
TXO8: TXO8.1, TXO8.3, U9.2
TXO9: TXO9.1, TXO9.3, U10.2
TXO10: TXO10.1, TXO10.3, U11.2
TXO11: TXO11.1, TXO11.3, U12.2
TXO12: TXO12.1, TXO12.3, U13.2
TXO13: TXO13.1, TXO13.3, U14.2
TXO14: TXO14.1, TXO14.3, U15.2
TXO15: TXO15.1, TXO15.3, U16.2
USB_D+: J5.3, U2.5
USB_D+1: J6.3, U1.5
USB_D+2: J9.3, U3.5
USB_D+3: J12.3, U4.5
USB_D+4: J15.3, U5.5
USB_D+5: J18.3, U6.5
USB_D+6: J21.3, U7.5
USB_D+7: J24.3, U8.5
USB_D+8: J27.3, U9.5
USB_D+9: J30.3, U10.5
USB_D+10: J33.3, U11.5
USB_D+11: J36.3, U12.5
USB_D+12: J39.3, U13.5
USB_D+13: J42.3, U14.5
USB_D+14: J45.3, U15.5
USB_D+15: J48.3, U16.5
USB_D-: J5.5, U2.6
USB_D-1: J6.5, U1.6
USB_D-2: J9.5, U3.6
USB_D-3: J12.5, U4.6
USB_D-4: J15.5, U5.6
USB_D-5: J18.5, U6.6
USB_D-6: J21.5, U7.6
USB_D-7: J24.5, U8.6
USB_D-8: J27.5, U9.6
USB_D-9: J30.5, U10.6
USB_D-10: J33.5, U11.6
USB_D-11: J36.5, U12.6
USB_D-12: J39.5, U13.6
USB_D-13: J42.5, U14.6
USB_D-14: J45.5, U15.6
USB_D-15: J48.5, U16.6

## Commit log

2020-10-19 Added the Eagle files
2020-10-20 Adding production panel (8x2)
2020-10-22 Changed to the CH340C
2020-11-26 Updates for v10
2021-02-25 Update README
    Updating README for release.
2021-02-25 Update README
    Adding link to Asset Tracker product page.

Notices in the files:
parts and their libraries:
SparkFun-Aesthetics: Licensing: CC v3.0 Share-Alike You are welcome to use this library for commercial purposes.
SparkFun-Aesthetics: Released under the Creative Commons Attribution Share-Alike 4.0 License
SparkFun-Aesthetics: https://creativecommons.org/licenses/by-sa/4.0
